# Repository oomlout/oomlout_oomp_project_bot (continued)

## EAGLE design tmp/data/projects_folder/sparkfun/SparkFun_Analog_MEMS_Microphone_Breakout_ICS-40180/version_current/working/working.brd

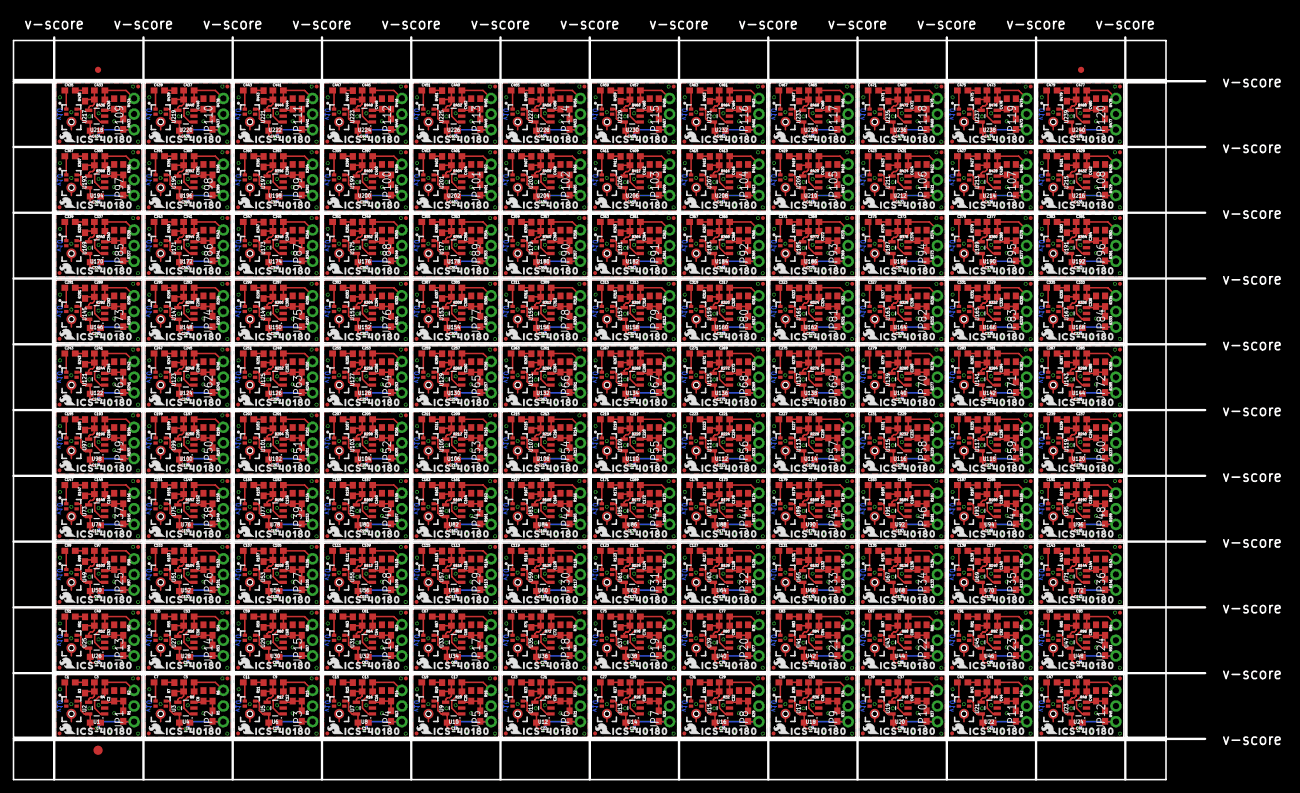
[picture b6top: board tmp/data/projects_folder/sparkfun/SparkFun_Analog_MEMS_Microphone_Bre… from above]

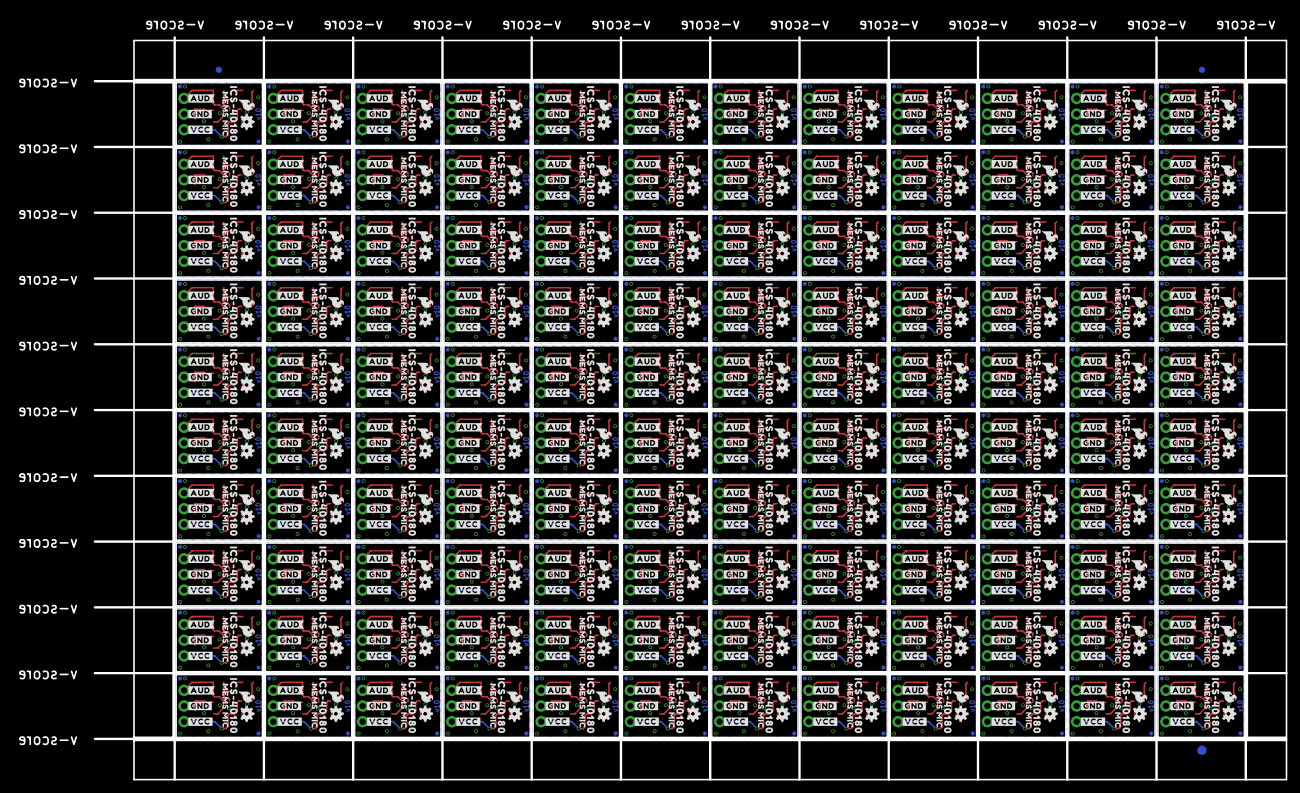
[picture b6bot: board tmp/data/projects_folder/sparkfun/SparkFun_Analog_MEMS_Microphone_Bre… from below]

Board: 2 copper layers, 193.3 x 120.4 mm, 2886 parts (1083 on the bottom side), 840 nets.

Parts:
C1, C7, C11, C15, C19, C23, C27, C31, C35, C39, C43, C47, C51, C55, C59, C63, C67, C71, C75, C79, C83, C87, C91, C95, C99, C103, C107, C111, C115, C119, C123, C127, C131, C135, C139, C143, C147, C151, C155, C159, C163, C167, C171, C175, C179, C183, C187, C191, C195, C199, C203, C207, C211, C215, C219, C223, C227, C231, C235, C239, C243, C247, C251, C255, C259, C263, C267, C271, C275, C279, C283, C287, C291, C295, C299, C303, C307, C311, C315, C319, C323, C327, C331, C335, C339, C343, C347, C351, C355, C359, C363, C367, C371, C375, C379, C383, C387, C391, C395, C399, C403, C407, C411, C415, C419, C423, C427, C431, C435, C439, C443, C447, C451, C455, C459, C463, C467, C471, C475, C479: 4.7uF; 0603
C2, C8, C12, C16, C20, C24, C28, C32, C36, C40, C44, C48, C52, C56, C60, C64, C68, C72, C76, C80, C84, C88, C92, C96, C100, C104, C108, C112, C116, C120, C124, C128, C132, C136, C140, C144, C148, C152, C156, C160, C164, C168, C172, C176, C180, C184, C188, C192, C196, C200, C204, C208, C212, C216, C220, C224, C228, C232, C236, C240, C244, C248, C252, C256, C260, C264, C268, C272, C276, C280, C284, C288, C292, C296, C300, C304, C308, C312, C316, C320, C324, C328, C332, C336, C340, C344, C348, C352, C356, C360, C364, C368, C372, C376, C380, C384, C388, C392, C396, C400, C404, C408, C412, C416, C420, C424, C428, C432, C436, C440, C444, C448, C452, C456, C460, C464, C468, C472, C476, C480: 1.0uF; 0603
C3, C5, C9, C13, C17, C21, C25, C29, C33, C37, C41, C45, C49, C53, C57, C61, C65, C69, C73, C77, C81, C85, C89, C93, C97, C101, C105, C109, C113, C117, C121, C125, C129, C133, C137, C141, C145, C149, C153, C157, C161, C165, C169, C173, C177, C181, C185, C189, C193, C197, C201, C205, C209, C213, C217, C221, C225, C229, C233, C237, C241, C245, C249, C253, C257, C261, C265, C269, C273, C277, C281, C285, C289, C293, C297, C301, C305, C309, C313, C317, C321, C325, C329, C333, C337, C341, C345, C349, C353, C357, C361, C365, C369, C373, C377, C381, C385, C389, C393, C397, C401, C405, C409, C413, C417, C421, C425, C429, C433, C437, C441, C445, C449, C453, C457, C461, C465, C469, C473, C477: 27pF; 0603
C4, C6, C10, C14, C18, C22, C26, C30, C34, C38, C42, C46, C50, C54, C58, C62, C66, C70, C74, C78, C82, C86, C90, C94, C98, C102, C106, C110, C114, C118, C122, C126, C130, C134, C138, C142, C146, C150, C154, C158, C162, C166, C170, C174, C178, C182, C186, C190, C194, C198, C202, C206, C210, C214, C218, C222, C226, C230, C234, C238, C242, C246, C250, C254, C258, C262, C266, C270, C274, C278, C282, C286, C290, C294, C298, C302, C306, C310, C314, C318, C322, C326, C330, C334, C338, C342, C346, C350, C354, C358, C362, C366, C370, C374, C378, C382, C386, C390, C394, C398, C402, C406, C410, C414, C418, C422, C426, C430, C434, C438, C442, C446, C450, C454, C458, C462, C466, C470, C474, C478: 0.1uF; 0603
E$1, E$2, E$3, E$4: FIDUCIAL-1X2
E$5, E$6: FIDUCIAL-1.5X3
FD1, FD2, FD3, FD4, FD5, FD6, FD7, FD8, FD9, FD10, FD11, FD12, FD13, FD14, FD15, FD16, FD17, FD18, FD19, FD20, FD21, FD22, FD23, FD24, FD25, FD26, FD27, FD28, FD29, FD30, FD31, FD32, FD33, FD34, FD35, FD36, FD37, FD38, FD39, FD40, FD41, FD42, FD43, FD44, FD45, FD46, FD47, FD48, FD49, FD50, FD51, FD52, FD53, FD54, FD55, FD56, FD57, FD58, FD59, FD60, FD61, FD62, FD63, FD64, FD65, FD66, FD67, FD68, FD69, FD70, FD71, FD72, FD73, FD74, FD75, FD76, FD77, FD78, FD79, FD80, FD81, FD82, FD83, FD84, FD85, FD86, FD87, FD88, FD89, FD90, FD91, FD92, FD93, FD94, FD95, FD96, FD97, FD98, FD99, FD100, FD101, FD102, FD103, FD104, FD105, FD106, FD107, FD108, FD109, FD110, FD111, FD112, FD113, FD114, FD115, FD116, FD117, FD118, FD119, FD120, FD121, FD122, FD123, FD124, FD125, FD126, FD127, FD128, FD129, FD130, FD131, FD132, FD133, FD134, FD135, FD136, FD137, FD138, FD139, FD140, FD141, FD142, FD143, FD144, FD145, FD146, FD147, FD148, FD149, FD150, FD151, FD152, FD153, FD154, FD155, FD156, FD157, FD158, FD159, FD160, FD161, FD162, FD163, FD164, FD165, FD166, FD167, FD168, FD169, FD170, FD171, FD172, FD173, FD174, FD175, FD176, FD177, FD178, FD179, FD180, FD181, FD182, FD183, FD184, FD185, FD186, FD187, FD188, FD189, FD190, FD191, FD192, FD193, FD194, FD195, FD196, FD197, FD198, FD199, FD200, FD201, FD202, FD203, FD204, FD205, FD206, FD207, FD208, FD209, FD210, FD211, FD212, FD213, FD214, FD215, FD216, FD217, FD218, FD219, FD220, FD221, FD222, FD223, FD224, FD225, FD226, FD227, FD228, FD229, FD230, FD231, FD232, FD233, FD234, FD235, FD236, FD237, FD238, FD239, FD240, FD241, FD242, FD243, FD244, FD245, FD246, FD247, FD248, FD249, FD250, FD251, FD252, FD253, FD254, FD255, FD256, FD257, FD258, FD259, FD260, FD261, FD262, FD263, FD264, FD265, FD266, FD267, FD268, FD269, FD270, FD271, FD272, FD273, FD274, FD275, FD276, FD277, FD278, FD279, FD280, FD281, FD282, FD283, FD284, FD285, FD286, FD287, FD288, FD289, FD290, FD291, FD292, FD293, FD294, FD295, FD296, FD297, FD298, FD299, FD300, FD301, FD302, FD303, FD304, FD305, FD306, FD307, FD308, FD309, FD310, FD311, FD312, FD313, FD314, FD315, FD316, FD317, FD318, FD319, FD320, FD321, FD322, FD323, FD324, FD325, FD326, FD327, FD328, FD329, FD330, FD331, FD332, FD333, FD334, FD335, FD336, FD337, FD338, FD339, FD340, FD341, FD342, FD343, FD344, FD345, FD346, FD347, FD348, FD349, FD350, FD351, FD352, FD353, FD354, FD355, FD356, FD357, FD358, FD359, FD360, FD361, FD362, FD363, FD364, FD365, FD366, FD367, FD368, FD369, FD370, FD371, FD372, FD373, FD374, FD375, FD376, FD377, FD378, FD379, FD380, FD381, FD382, FD383, FD384, FD385, FD386, FD387, FD388, FD389, FD390, FD391, FD392, FD393, FD394, FD395, FD396, FD397, FD398, FD399, FD400, FD401, FD402, FD403, FD404, FD405, FD406, FD407, FD408, FD409, FD410, FD411, FD412, FD413, FD414, FD415, FD416, FD417, FD418, FD419, FD420, FD421, FD422, FD423, FD424, FD425, FD426, FD427, FD428, FD429, FD430, FD431, FD432, FD433, FD434, FD435, FD436, FD437, FD438, FD439, FD440, FD441, FD442, FD443, FD444, FD445, FD446, FD447, FD448, FD449, FD450, FD451, FD452, FD453, FD454, FD455, FD456, FD457, FD458, FD459, FD460, FD461, FD462, FD463, FD464, FD465, FD466, FD467, FD468, FD469, FD470, FD471, FD472, FD473, FD474, FD475, FD476, FD477, FD478, FD479, FD480: FIDUCIALUFIDUCIAL; FIDUCIAL-MICRO
JP1, JP2, JP3, JP4, JP5, JP6, JP7, JP8, JP9, JP10, JP11, JP12, JP13, JP14, JP15, JP16, JP17, JP18, JP19, JP20, JP21, JP22, JP23, JP24, JP25, JP26, JP27, JP28, JP29, JP30, JP31, JP32, JP33, JP34, JP35, JP36, JP37, JP38, JP39, JP40, JP41, JP42, JP43, JP44, JP45, JP46, JP47, JP48, JP49, JP50, JP51, JP52, JP53, JP54, JP55, JP56, JP57, JP58, JP59, JP60, JP61, JP62, JP63, JP64, JP65, JP66, JP67, JP68, JP69, JP70, JP71, JP72, JP73, JP74, JP75, JP76, JP77, JP78, JP79, JP80, JP81, JP82, JP83, JP84, JP85, JP86, JP87, JP88, JP89, JP90, JP91, JP92, JP93, JP94, JP95, JP96, JP97, JP98, JP99, JP100, JP101, JP102, JP103, JP104, JP105, JP106, JP107, JP108, JP109, JP110, JP111, JP112, JP113, JP114, JP115, JP116, JP117, JP118, JP119, JP120: 1X03_NO_SILK
LOGO1, LOGO3, LOGO4, LOGO6, LOGO7, LOGO9, LOGO10, LOGO12, LOGO13, LOGO15, LOGO16, LOGO18, LOGO19, LOGO21, LOGO22, LOGO24, LOGO25, LOGO27, LOGO28, LOGO30, LOGO31, LOGO33, LOGO34, LOGO36, LOGO37, LOGO39, LOGO40, LOGO42, LOGO43, LOGO45, LOGO46, LOGO48, LOGO49, LOGO51, LOGO52, LOGO54, LOGO55, LOGO57, LOGO58, LOGO60, LOGO61, LOGO63, LOGO64, LOGO66, LOGO67, LOGO69, LOGO70, LOGO72, LOGO73, LOGO75, LOGO76, LOGO78, LOGO79, LOGO81, LOGO82, LOGO84, LOGO85, LOGO87, LOGO88, LOGO90, LOGO91, LOGO93, LOGO94, LOGO96, LOGO97, LOGO99, LOGO100, LOGO102, LOGO103, LOGO105, LOGO106, LOGO108, LOGO109, LOGO111, LOGO112, LOGO114, LOGO115, LOGO117, LOGO118, LOGO120, LOGO121, LOGO123, LOGO124, LOGO126, LOGO127, LOGO129, LOGO130, LOGO132, LOGO133, LOGO135, LOGO136, LOGO138, LOGO139, LOGO141, LOGO142, LOGO144, LOGO145, LOGO147, LOGO148, LOGO150, LOGO151, LOGO153, LOGO154, LOGO156, LOGO157, LOGO159, LOGO160, LOGO162, LOGO163, LOGO165, LOGO166, LOGO168, LOGO169, LOGO171, LOGO172, LOGO174, LOGO175, LOGO177, LOGO178, LOGO180, LOGO181, LOGO183, LOGO184, LOGO186, LOGO187, LOGO189, LOGO190, LOGO192, LOGO193, LOGO195, LOGO196, LOGO198, LOGO199, LOGO201, LOGO202, LOGO204, LOGO205, LOGO207, LOGO208, LOGO210, LOGO211, LOGO213, LOGO214, LOGO216, LOGO217, LOGO219, LOGO220, LOGO222, LOGO223, LOGO225, LOGO226, LOGO228, LOGO229, LOGO231, LOGO232, LOGO234, LOGO235, LOGO237, LOGO238, LOGO240, LOGO241, LOGO243, LOGO244, LOGO246, LOGO247, LOGO249, LOGO250, LOGO252, LOGO253, LOGO255, LOGO256, LOGO258, LOGO259, LOGO261, LOGO262, LOGO264, LOGO265, LOGO267, LOGO268, LOGO270, LOGO271, LOGO273, LOGO274, LOGO276, LOGO277, LOGO279, LOGO280, LOGO282, LOGO283, LOGO285, LOGO286, LOGO288, LOGO289, LOGO291, LOGO292, LOGO294, LOGO295, LOGO297, LOGO298, LOGO300, LOGO301, LOGO303, LOGO304, LOGO306, LOGO307, LOGO309, LOGO310, LOGO312, LOGO313, LOGO315, LOGO316, LOGO318, LOGO319, LOGO321, LOGO322, LOGO324, LOGO325, LOGO327, LOGO328, LOGO330, LOGO331, LOGO333, LOGO334, LOGO336, LOGO337, LOGO339, LOGO340, LOGO342, LOGO343, LOGO345, LOGO346, LOGO348, LOGO349, LOGO351, LOGO352, LOGO354, LOGO355, LOGO357, LOGO358, LOGO360: SFE_LOGO_FLAME.1_INCH; SFE_LOGO_FLAME_.1
LOGO2, LOGO5, LOGO8, LOGO11, LOGO14, LOGO17, LOGO20, LOGO23, LOGO26, LOGO29, LOGO32, LOGO35, LOGO38, LOGO41, LOGO44, LOGO47, LOGO50, LOGO53, LOGO56, LOGO59, LOGO62, LOGO65, LOGO68, LOGO71, LOGO74, LOGO77, LOGO80, LOGO83, LOGO86, LOGO89, LOGO92, LOGO95, LOGO98, LOGO101, LOGO104, LOGO107, LOGO110, LOGO113, LOGO116, LOGO119, LOGO122, LOGO125, LOGO128, LOGO131, LOGO134, LOGO137, LOGO140, LOGO143, LOGO146, LOGO149, LOGO152, LOGO155, LOGO158, LOGO161, LOGO164, LOGO167, LOGO170, LOGO173, LOGO176, LOGO179, LOGO182, LOGO185, LOGO188, LOGO191, LOGO194, LOGO197, LOGO200, LOGO203, LOGO206, LOGO209, LOGO212, LOGO215, LOGO218, LOGO221, LOGO224, LOGO227, LOGO230, LOGO233, LOGO236, LOGO239, LOGO242, LOGO245, LOGO248, LOGO251, LOGO254, LOGO257, LOGO260, LOGO263, LOGO266, LOGO269, LOGO272, LOGO275, LOGO278, LOGO281, LOGO284, LOGO287, LOGO290, LOGO293, LOGO296, LOGO299, LOGO302, LOGO305, LOGO308, LOGO311, LOGO314, LOGO317, LOGO320, LOGO323, LOGO326, LOGO329, LOGO332, LOGO335, LOGO338, LOGO341, LOGO344, LOGO347, LOGO350, LOGO353, LOGO356, LOGO359: OSHW-LOGOMINI; OSHW-LOGO-MINI
R1, R2, R5, R6, R9, R10, R13, R14, R17, R18, R21, R22, R25, R26, R29, R30, R33, R34, R37, R38, R41, R42, R45, R46, R49, R50, R53, R54, R57, R58, R61, R62, R65, R66, R69, R70, R73, R74, R77, R78, R81, R82, R85, R86, R89, R90, R93, R94, R97, R98, R101, R102, R105, R106, R109, R110, R113, R114, R117, R118, R121, R122, R125, R126, R129, R130, R133, R134, R137, R138, R141, R142, R145, R146, R149, R150, R153, R154, R157, R158, R161, R162, R165, R166, R169, R170, R173, R174, R177, R178, R181, R182, R185, R186, R189, R190, R193, R194, R197, R198, R201, R202, R205, R206, R209, R210, R213, R214, R217, R218, R221, R222, R225, R226, R229, R230, R233, R234, R237, R238, R241, R242, R245, R246, R249, R250, R253, R254, R257, R258, R261, R262, R265, R266, R269, R270, R273, R274, R277, R278, R281, R282, R285, R286, R289, R290, R293, R294, R297, R298, R301, R302, R305, R306, R309, R310, R313, R314, R317, R318, R321, R322, R325, R326, R329, R330, R333, R334, R337, R338, R341, R342, R345, R346, R349, R350, R353, R354, R357, R358, R361, R362, R365, R366, R369, R370, R373, R374, R377, R378, R381, R382, R385, R386, R389, R390, R393, R394, R397, R398, R401, R402, R405, R406, R409, R410, R413, R414, R417, R418, R421, R422, R425, R426, R429, R430, R433, R434, R437, R438, R441, R442, R445, R446, R449, R450, R453, R454, R457, R458, R461, R462, R465, R466, R469, R470, R473, R474, R477, R478: 10k; 0603
R3, R7, R11, R15, R19, R23, R27, R31, R35, R39, R43, R47, R51, R55, R59, R63, R67, R71, R75, R79, R83, R87, R91, R95, R99, R103, R107, R111, R115, R119, R123, R127, R131, R135, R139, R143, R147, R151, R155, R159, R163, R167, R171, R175, R179, R183, R187, R191, R195, R199, R203, R207, R211, R215, R219, R223, R227, R231, R235, R239, R243, R247, R251, R255, R259, R263, R267, R271, R275, R279, R283, R287, R291, R295, R299, R303, R307, R311, R315, R319, R323, R327, R331, R335, R339, R343, R347, R351, R355, R359, R363, R367, R371, R375, R379, R383, R387, R391, R395, R399, R403, R407, R411, R415, R419, R423, R427, R431, R435, R439, R443, R447, R451, R455, R459, R463, R467, R471, R475, R479: 4.7k; 0603
R4, R8, R12, R16, R20, R24, R28, R32, R36, R40, R44, R48, R52, R56, R60, R64, R68, R72, R76, R80, R84, R88, R92, R96, R100, R104, R108, R112, R116, R120, R124, R128, R132, R136, R140, R144, R148, R152, R156, R160, R164, R168, R172, R176, R180, R184, R188, R192, R196, R200, R204, R208, R212, R216, R220, R224, R228, R232, R236, R240, R244, R248, R252, R256, R260, R264, R268, R272, R276, R280, R284, R288, R292, R296, R300, R304, R308, R312, R316, R320, R324, R328, R332, R336, R340, R344, R348, R352, R356, R360, R364, R368, R372, R376, R380, R384, R388, R392, R396, R400, R404, R408, R412, R416, R420, R424, R428, R432, R436, R440, R444, R448, R452, R456, R460, R464, R468, R472, R476, R480: 300k; 0603
U1, U4, U6, U8, U10, U12, U14, U16, U18, U20, U22, U24, U26, U28, U30, U32, U34, U36, U38, U40, U42, U44, U46, U48, U50, U52, U54, U56, U58, U60, U62, U64, U66, U68, U70, U72, U74, U76, U78, U80, U82, U84, U86, U88, U90, U92, U94, U96, U98, U100, U102, U104, U106, U108, U110, U112, U114, U116, U118, U120, U122, U124, U126, U128, U130, U132, U134, U136, U138, U140, U142, U144, U146, U148, U150, U152, U154, U156, U158, U160, U162, U164, U166, U168, U170, U172, U174, U176, U178, U180, U182, U184, U186, U188, U190, U192, U194, U196, U198, U200, U202, U204, U206, U208, U210, U212, U214, U216, U218, U220, U222, U224, U226, U228, U230, U232, U234, U236, U238, U240: OPA344; SOT23-5
U2, U3, U5, U7, U9, U11, U13, U15, U17, U19, U21, U23, U25, U27, U29, U31, U33, U35, U37, U39, U41, U43, U45, U47, U49, U51, U53, U55, U57, U59, U61, U63, U65, U67, U69, U71, U73, U75, U77, U79, U81, U83, U85, U87, U89, U91, U93, U95, U97, U99, U101, U103, U105, U107, U109, U111, U113, U115, U117, U119, U121, U123, U125, U127, U129, U131, U133, U135, U137, U139, U141, U143, U145, U147, U149, U151, U153, U155, U157, U159, U161, U163, U165, U167, U169, U171, U173, U175, U177, U179, U181, U183, U185, U187, U189, U191, U193, U195, U197, U199, U201, U203, U205, U207, U209, U211, U213, U215, U217, U219, U221, U223, U225, U227, U229, U231, U233, U235, U237, U239: ICS40180
U$1, U$6, U$7, U$12, U$13, U$18, U$19, U$24, U$25, U$30, U$31, U$36, U$37, U$42, U$43, U$48, U$49, U$54, U$55, U$60, U$61, U$66, U$67, U$72, U$73, U$78, U$79, U$84, U$85, U$90, U$91, U$96, U$97, U$102, U$103, U$108, U$109, U$114, U$115, U$120, U$121, U$126, U$127, U$132, U$133, U$138, U$139, U$144, U$145, U$150, U$151, U$156, U$157, U$162, U$163, U$168, U$169, U$174, U$175, U$180, U$181, U$186, U$187, U$192, U$193, U$198, U$199, U$204, U$205, U$210, U$211, U$216, U$217, U$222, U$223, U$228, U$229, U$234, U$235, U$240, U$241, U$246, U$247, U$252, U$253, U$258, U$259, U$264, U$265, U$270, U$271, U$276, U$277, U$282, U$283, U$288, U$289, U$294, U$295, U$300, U$301, U$306, U$307, U$312, U$313, U$318, U$319, U$324, U$325, U$330, U$331, U$336, U$337, U$342, U$343, U$348, U$349, U$354, U$355, U$360, U$361, U$366, U$367, U$372, U$373, U$378, U$379, U$384, U$385, U$390, U$391, U$396, U$397, U$402, U$403, U$408, U$409, U$414, U$415, U$420, U$421, U$426, U$427, U$432, U$433, U$438, U$439, U$444, U$445, U$450, U$451, U$456, U$457, U$462, U$463, U$468, U$469, U$474, U$475, U$480, U$481, U$486, U$487, U$492, U$493, U$498, U$499, U$504, U$505, U$510, U$511, U$516, U$517, U$522, U$523, U$528, U$529, U$534, U$535, U$540, U$541, U$546, U$547, U$552, U$553, U$558, U$559, U$564, U$565, U$570, U$571, U$576, U$577, U$582, U$583, U$588, U$589, U$594, U$595, U$600, U$601, U$606, U$607, U$612, U$613, U$618, U$619, U$624, U$625, U$630, U$631, U$636, U$637, U$642, U$643, U$648, U$649, U$654, U$655, U$660, U$661, U$666, U$667, U$672, U$673, U$678, U$679, U$684, U$685, U$690, U$691, U$696, U$697, U$702, U$703, U$708, U$709, U$714, U$715, U$720: ICS#401800
U$2, U$8, U$14, U$20, U$26, U$32, U$38, U$44, U$50, U$56, U$62, U$68, U$74, U$80, U$86, U$92, U$98, U$104, U$110, U$116, U$122, U$128, U$134, U$140, U$146, U$152, U$158, U$164, U$170, U$176, U$182, U$188, U$194, U$200, U$206, U$212, U$218, U$224, U$230, U$236, U$242, U$248, U$254, U$260, U$266, U$272, U$278, U$284, U$290, U$296, U$302, U$308, U$314, U$320, U$326, U$332, U$338, U$344, U$350, U$356, U$362, U$368, U$374, U$380, U$386, U$392, U$398, U$404, U$410, U$416, U$422, U$428, U$434, U$440, U$446, U$452, U$458, U$464, U$470, U$476, U$482, U$488, U$494, U$500, U$506, U$512, U$518, U$524, U$530, U$536, U$542, U$548, U$554, U$560, U$566, U$572, U$578, U$584, U$590, U$596, U$602, U$608, U$614, U$620, U$626, U$632, U$638, U$644, U$650, U$656, U$662, U$668, U$674, U$680, U$686, U$692, U$698, U$704, U$710, U$716: MEMS_MIC0
U$3, U$9, U$15, U$21, U$27, U$33, U$39, U$45, U$51, U$57, U$63, U$69, U$75, U$81, U$87, U$93, U$99, U$105, U$111, U$117, U$123, U$129, U$135, U$141, U$147, U$153, U$159, U$165, U$171, U$177, U$183, U$189, U$195, U$201, U$207, U$213, U$219, U$225, U$231, U$237, U$243, U$249, U$255, U$261, U$267, U$273, U$279, U$285, U$291, U$297, U$303, U$309, U$315, U$321, U$327, U$333, U$339, U$345, U$351, U$357, U$363, U$369, U$375, U$381, U$387, U$393, U$399, U$405, U$411, U$417, U$423, U$429, U$435, U$441, U$447, U$453, U$459, U$465, U$471, U$477, U$483, U$489, U$495, U$501, U$507, U$513, U$519, U$525, U$531, U$537, U$543, U$549, U$555, U$561, U$567, U$573, U$579, U$585, U$591, U$597, U$603, U$609, U$615, U$621, U$627, U$633, U$639, U$645, U$651, U$657, U$663, U$669, U$675, U$681, U$687, U$693, U$699, U$705, U$711, U$717: #GND#0
U$4, U$10, U$16, U$22, U$28, U$34, U$40, U$46, U$52, U$58, U$64, U$70, U$76, U$82, U$88, U$94, U$100, U$106, U$112, U$118, U$124, U$130, U$136, U$142, U$148, U$154, U$160, U$166, U$172, U$178, U$184, U$190, U$196, U$202, U$208, U$214, U$220, U$226, U$232, U$238, U$244, U$250, U$256, U$262, U$268, U$274, U$280, U$286, U$292, U$298, U$304, U$310, U$316, U$322, U$328, U$334, U$340, U$346, U$352, U$358, U$364, U$370, U$376, U$382, U$388, U$394, U$400, U$406, U$412, U$418, U$424, U$430, U$436, U$442, U$448, U$454, U$460, U$466, U$472, U$478, U$484, U$490, U$496, U$502, U$508, U$514, U$520, U$526, U$532, U$538, U$544, U$550, U$556, U$562, U$568, U$574, U$580, U$586, U$592, U$598, U$604, U$610, U$616, U$622, U$628, U$634, U$640, U$646, U$652, U$658, U$664, U$670, U$676, U$682, U$688, U$694, U$700, U$706, U$712, U$718: #VCC#0
U$5, U$11, U$17, U$23, U$29, U$35, U$41, U$47, U$53, U$59, U$65, U$71, U$77, U$83, U$89, U$95, U$101, U$107, U$113, U$119, U$125, U$131, U$137, U$143, U$149, U$155, U$161, U$167, U$173, U$179, U$185, U$191, U$197, U$203, U$209, U$215, U$221, U$227, U$233, U$239, U$245, U$251, U$257, U$263, U$269, U$275, U$281, U$287, U$293, U$299, U$305, U$311, U$317, U$323, U$329, U$335, U$341, U$347, U$353, U$359, U$365, U$371, U$377, U$383, U$389, U$395, U$401, U$407, U$413, U$419, U$425, U$431, U$437, U$443, U$449, U$455, U$461, U$467, U$473, U$479, U$485, U$491, U$497, U$503, U$509, U$515, U$521, U$527, U$533, U$539, U$545, U$551, U$557, U$563, U$569, U$575, U$581, U$587, U$593, U$599, U$605, U$611, U$617, U$623, U$629, U$635, U$641, U$647, U$653, U$659, U$665, U$671, U$677, U$683, U$689, U$695, U$701, U$707, U$713, U$719: #AUD#0

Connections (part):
AUD: C3.2, JP1.3, R4.1, U1.1
AUD1: C5.2, JP2.3, R8.1, U4.1
AUD2: C9.2, JP3.3, R12.1, U6.1
AUD3: C13.2, JP4.3, R16.1, U8.1
AUD4: C17.2, JP5.3, R20.1, U10.1
AUD5: C21.2, JP6.3, R24.1, U12.1
AUD6: C25.2, JP7.3, R28.1, U14.1
AUD7: C29.2, JP8.3, R32.1, U16.1
AUD8: C33.2, JP9.3, R36.1, U18.1
AUD9: C37.2, JP10.3, R40.1, U20.1
AUD10: C41.2, JP11.3, R44.1, U22.1
AUD11: C45.2, JP12.3, R48.1, U24.1
AUD12: C49.2, JP13.3, R52.1, U26.1
AUD13: C53.2, JP14.3, R56.1, U28.1
AUD14: C57.2, JP15.3, R60.1, U30.1
AUD15: C61.2, JP16.3, R64.1, U32.1
AUD16: C65.2, JP17.3, R68.1, U34.1
AUD17: C69.2, JP18.3, R72.1, U36.1
AUD18: C73.2, JP19.3, R76.1, U38.1
AUD19: C77.2, JP20.3, R80.1, U40.1
AUD20: C81.2, JP21.3, R84.1, U42.1
AUD21: C85.2, JP22.3, R88.1, U44.1
AUD22: C89.2, JP23.3, R92.1, U46.1
AUD23: C93.2, JP24.3, R96.1, U48.1
AUD24: C97.2, JP25.3, R100.1, U50.1
AUD25: C101.2, JP26.3, R104.1, U52.1
AUD26: C105.2, JP27.3, R108.1, U54.1
AUD27: C109.2, JP28.3, R112.1, U56.1
AUD28: C113.2, JP29.3, R116.1, U58.1
AUD29: C117.2, JP30.3, R120.1, U60.1
AUD30: C121.2, JP31.3, R124.1, U62.1
AUD31: C125.2, JP32.3, R128.1, U64.1
AUD32: C129.2, JP33.3, R132.1, U66.1
AUD33: C133.2, JP34.3, R136.1, U68.1
AUD34: C137.2, JP35.3, R140.1, U70.1
AUD35: C141.2, JP36.3, R144.1, U72.1
AUD36: C145.2, JP37.3, R148.1, U74.1
AUD37: C149.2, JP38.3, R152.1, U76.1
AUD38: C153.2, JP39.3, R156.1, U78.1
AUD39: C157.2, JP40.3, R160.1, U80.1
AUD40: C161.2, JP41.3, R164.1, U82.1
AUD41: C165.2, JP42.3, R168.1, U84.1
AUD42: C169.2, JP43.3, R172.1, U86.1
AUD43: C173.2, JP44.3, R176.1, U88.1
AUD44: C177.2, JP45.3, R180.1, U90.1
AUD45: C181.2, JP46.3, R184.1, U92.1
AUD46: C185.2, JP47.3, R188.1, U94.1
AUD47: C189.2, JP48.3, R192.1, U96.1
AUD48: C193.2, JP49.3, R196.1, U98.1
AUD49: C197.2, JP50.3, R200.1, U100.1
AUD50: C201.2, JP51.3, R204.1, U102.1
AUD51: C205.2, JP52.3, R208.1, U104.1
AUD52: C209.2, JP53.3, R212.1, U106.1
AUD53: C213.2, JP54.3, R216.1, U108.1
AUD54: C217.2, JP55.3, R220.1, U110.1
AUD55: C221.2, JP56.3, R224.1, U112.1
AUD56: C225.2, JP57.3, R228.1, U114.1
AUD57: C229.2, JP58.3, R232.1, U116.1
AUD58: C233.2, JP59.3, R236.1, U118.1
AUD59: C237.2, JP60.3, R240.1, U120.1
AUD60: C241.2, JP61.3, R244.1, U122.1
AUD61: C245.2, JP62.3, R248.1, U124.1
AUD62: C249.2, JP63.3, R252.1, U126.1
AUD63: C253.2, JP64.3, R256.1, U128.1
AUD64: C257.2, JP65.3, R260.1, U130.1
AUD65: C261.2, JP66.3, R264.1, U132.1
AUD66: C265.2, JP67.3, R268.1, U134.1
AUD67: C269.2, JP68.3, R272.1, U136.1
AUD68: C273.2, JP69.3, R276.1, U138.1
AUD69: C277.2, JP70.3, R280.1, U140.1
AUD70: C281.2, JP71.3, R284.1, U142.1
AUD71: C285.2, JP72.3, R288.1, U144.1
AUD72: C289.2, JP73.3, R292.1, U146.1
AUD73: C293.2, JP74.3, R296.1, U148.1
AUD74: C297.2, JP75.3, R300.1, U150.1
AUD75: C301.2, JP76.3, R304.1, U152.1
AUD76: C305.2, JP77.3, R308.1, U154.1
AUD77: C309.2, JP78.3, R312.1, U156.1
AUD78: C313.2, JP79.3, R316.1, U158.1
AUD79: C317.2, JP80.3, R320.1, U160.1
AUD80: C321.2, JP81.3, R324.1, U162.1
AUD81: C325.2, JP82.3, R328.1, U164.1
AUD82: C329.2, JP83.3, R332.1, U166.1
AUD83: C333.2, JP84.3, R336.1, U168.1
AUD84: C337.2, JP85.3, R340.1, U170.1
AUD85: C341.2, JP86.3, R344.1, U172.1
AUD86: C345.2, JP87.3, R348.1, U174.1
AUD87: C349.2, JP88.3, R352.1, U176.1
AUD88: C353.2, JP89.3, R356.1, U178.1
AUD89: C357.2, JP90.3, R360.1, U180.1
AUD90: C361.2, JP91.3, R364.1, U182.1
AUD91: C365.2, JP92.3, R368.1, U184.1
AUD92: C369.2, JP93.3, R372.1, U186.1
AUD93: C373.2, JP94.3, R376.1, U188.1
AUD94: C377.2, JP95.3, R380.1, U190.1
AUD95: C381.2, JP96.3, R384.1, U192.1
AUD96: C385.2, JP97.3, R388.1, U194.1
AUD97: C389.2, JP98.3, R392.1, U196.1
AUD98: C393.2, JP99.3, R396.1, U198.1
AUD99: C397.2, JP100.3, R400.1, U200.1
AUD100: C401.2, JP101.3, R404.1, U202.1
AUD101: C405.2, JP102.3, R408.1, U204.1
AUD102: C409.2, JP103.3, R412.1, U206.1
AUD103: C413.2, JP104.3, R416.1, U208.1
AUD104: C417.2, JP105.3, R420.1, U210.1
AUD105: C421.2, JP106.3, R424.1, U212.1
AUD106: C425.2, JP107.3, R428.1, U214.1
AUD107: C429.2, JP108.3, R432.1, U216.1
AUD108: C433.2, JP109.3, R436.1, U218.1
AUD109: C437.2, JP110.3, R440.1, U220.1
AUD110: C441.2, JP111.3, R444.1, U222.1
AUD111: C445.2, JP112.3, R448.1, U224.1
AUD112: C449.2, JP113.3, R452.1, U226.1
AUD113: C453.2, JP114.3, R456.1, U228.1
AUD114: C457.2, JP115.3, R460.1, U230.1
AUD115: C461.2, JP116.3, R464.1, U232.1
AUD116: C465.2, JP117.3, R468.1, U234.1
AUD117: C469.2, JP118.3, R472.1, U236.1
AUD118: C473.2, JP119.3, R476.1, U238.1
AUD119: C477.2, JP120.3, R480.1, U240.1
GND: C2.2, C4.1, JP1.2, R2.1, U1.2, U2.2, U2.3, U2.4
GND1: C6.1, C8.2, JP2.2, R6.1, U3.2, U3.3, U3.4, U4.2
GND2: C10.1, C12.2, JP3.2, R10.1, U5.2, U5.3, U5.4, U6.2
GND3: C14.1, C16.2, JP4.2, R14.1, U7.2, U7.3, U7.4, U8.2
GND4: C18.1, C20.2, JP5.2, R18.1, U9.2, U9.3, U9.4, U10.2
GND5: C22.1, C24.2, JP6.2, R22.1, U11.2, U11.3, U11.4, U12.2
GND6: C26.1, C28.2, JP7.2, R26.1, U13.2, U13.3, U13.4, U14.2
GND7: C30.1, C32.2, JP8.2, R30.1, U15.2, U15.3, U15.4, U16.2
GND8: C34.1, C36.2, JP9.2, R34.1, U17.2, U17.3, U17.4, U18.2
GND9: C38.1, C40.2, JP10.2, R38.1, U19.2, U19.3, U19.4, U20.2
GND10: C42.1, C44.2, JP11.2, R42.1, U21.2, U21.3, U21.4, U22.2
GND11: C46.1, C48.2, JP12.2, R46.1, U23.2, U23.3, U23.4, U24.2
GND12: C50.1, C52.2, JP13.2, R50.1, U25.2, U25.3, U25.4, U26.2
GND13: C54.1, C56.2, JP14.2, R54.1, U27.2, U27.3, U27.4, U28.2
GND14: C58.1, C60.2, JP15.2, R58.1, U29.2, U29.3, U29.4, U30.2
GND15: C62.1, C64.2, JP16.2, R62.1, U31.2, U31.3, U31.4, U32.2
GND16: C66.1, C68.2, JP17.2, R66.1, U33.2, U33.3, U33.4, U34.2
GND17: C70.1, C72.2, JP18.2, R70.1, U35.2, U35.3, U35.4, U36.2
GND18: C74.1, C76.2, JP19.2, R74.1, U37.2, U37.3, U37.4, U38.2
GND19: C78.1, C80.2, JP20.2, R78.1, U39.2, U39.3, U39.4, U40.2
GND20: C82.1, C84.2, JP21.2, R82.1, U41.2, U41.3, U41.4, U42.2
GND21: C86.1, C88.2, JP22.2, R86.1, U43.2, U43.3, U43.4, U44.2
GND22: C90.1, C92.2, JP23.2, R90.1, U45.2, U45.3, U45.4, U46.2
GND23: C94.1, C96.2, JP24.2, R94.1, U47.2, U47.3, U47.4, U48.2
GND24: C98.1, C100.2, JP25.2, R98.1, U49.2, U49.3, U49.4, U50.2
GND25: C102.1, C104.2, JP26.2, R102.1, U51.2, U51.3, U51.4, U52.2
GND26: C106.1, C108.2, JP27.2, R106.1, U53.2, U53.3, U53.4, U54.2
GND27: C110.1, C112.2, JP28.2, R110.1, U55.2, U55.3, U55.4, U56.2
GND28: C114.1, C116.2, JP29.2, R114.1, U57.2, U57.3, U57.4, U58.2
GND29: C118.1, C120.2, JP30.2, R118.1, U59.2, U59.3, U59.4, U60.2
GND30: C122.1, C124.2, JP31.2, R122.1, U61.2, U61.3, U61.4, U62.2
GND31: C126.1, C128.2, JP32.2, R126.1, U63.2, U63.3, U63.4, U64.2
GND32: C130.1, C132.2, JP33.2, R130.1, U65.2, U65.3, U65.4, U66.2
GND33: C134.1, C136.2, JP34.2, R134.1, U67.2, U67.3, U67.4, U68.2
GND34: C138.1, C140.2, JP35.2, R138.1, U69.2, U69.3, U69.4, U70.2
GND35: C142.1, C144.2, JP36.2, R142.1, U71.2, U71.3, U71.4, U72.2
GND36: C146.1, C148.2, JP37.2, R146.1, U73.2, U73.3, U73.4, U74.2
GND37: C150.1, C152.2, JP38.2, R150.1, U75.2, U75.3, U75.4, U76.2
GND38: C154.1, C156.2, JP39.2, R154.1, U77.2, U77.3, U77.4, U78.2
GND39: C158.1, C160.2, JP40.2, R158.1, U79.2, U79.3, U79.4, U80.2
GND40: C162.1, C164.2, JP41.2, R162.1, U81.2, U81.3, U81.4, U82.2
GND41: C166.1, C168.2, JP42.2, R166.1, U83.2, U83.3, U83.4, U84.2
GND42: C170.1, C172.2, JP43.2, R170.1, U85.2, U85.3, U85.4, U86.2
GND43: C174.1, C176.2, JP44.2, R174.1, U87.2, U87.3, U87.4, U88.2
GND44: C178.1, C180.2, JP45.2, R178.1, U89.2, U89.3, U89.4, U90.2
GND45: C182.1, C184.2, JP46.2, R182.1, U91.2, U91.3, U91.4, U92.2
GND46: C186.1, C188.2, JP47.2, R186.1, U93.2, U93.3, U93.4, U94.2
GND47: C190.1, C192.2, JP48.2, R190.1, U95.2, U95.3, U95.4, U96.2
GND48: C194.1, C196.2, JP49.2, R194.1, U97.2, U97.3, U97.4, U98.2
GND49: C198.1, C200.2, JP50.2, R198.1, U99.2, U99.3, U99.4, U100.2
GND50: C202.1, C204.2, JP51.2, R202.1, U101.2, U101.3, U101.4, U102.2
GND51: C206.1, C208.2, JP52.2, R206.1, U103.2, U103.3, U103.4, U104.2
GND52: C210.1, C212.2, JP53.2, R210.1, U105.2, U105.3, U105.4, U106.2
GND53: C214.1, C216.2, JP54.2, R214.1, U107.2, U107.3, U107.4, U108.2
GND54: C218.1, C220.2, JP55.2, R218.1, U109.2, U109.3, U109.4, U110.2
GND55: C222.1, C224.2, JP56.2, R222.1, U111.2, U111.3, U111.4, U112.2
GND56: C226.1, C228.2, JP57.2, R226.1, U113.2, U113.3, U113.4, U114.2
GND57: C230.1, C232.2, JP58.2, R230.1, U115.2, U115.3, U115.4, U116.2
GND58: C234.1, C236.2, JP59.2, R234.1, U117.2, U117.3, U117.4, U118.2
GND59: C238.1, C240.2, JP60.2, R238.1, U119.2, U119.3, U119.4, U120.2
GND60: C242.1, C244.2, JP61.2, R242.1, U121.2, U121.3, U121.4, U122.2
GND61: C246.1, C248.2, JP62.2, R246.1, U123.2, U123.3, U123.4, U124.2
GND62: C250.1, C252.2, JP63.2, R250.1, U125.2, U125.3, U125.4, U126.2
GND63: C254.1, C256.2, JP64.2, R254.1, U127.2, U127.3, U127.4, U128.2
GND64: C258.1, C260.2, JP65.2, R258.1, U129.2, U129.3, U129.4, U130.2
GND65: C262.1, C264.2, JP66.2, R262.1, U131.2, U131.3, U131.4, U132.2
GND66: C266.1, C268.2, JP67.2, R266.1, U133.2, U133.3, U133.4, U134.2
GND67: C270.1, C272.2, JP68.2, R270.1, U135.2, U135.3, U135.4, U136.2
GND68: C274.1, C276.2, JP69.2, R274.1, U137.2, U137.3, U137.4, U138.2
GND69: C278.1, C280.2, JP70.2, R278.1, U139.2, U139.3, U139.4, U140.2
GND70: C282.1, C284.2, JP71.2, R282.1, U141.2, U141.3, U141.4, U142.2
GND71: C286.1, C288.2, JP72.2, R286.1, U143.2, U143.3, U143.4, U144.2
GND72: C290.1, C292.2, JP73.2, R290.1, U145.2, U145.3, U145.4, U146.2
GND73: C294.1, C296.2, JP74.2, R294.1, U147.2, U147.3, U147.4, U148.2
GND74: C298.1, C300.2, JP75.2, R298.1, U149.2, U149.3, U149.4, U150.2
GND75: C302.1, C304.2, JP76.2, R302.1, U151.2, U151.3, U151.4, U152.2
GND76: C306.1, C308.2, JP77.2, R306.1, U153.2, U153.3, U153.4, U154.2
GND77: C310.1, C312.2, JP78.2, R310.1, U155.2, U155.3, U155.4, U156.2
GND78: C314.1, C316.2, JP79.2, R314.1, U157.2, U157.3, U157.4, U158.2
GND79: C318.1, C320.2, JP80.2, R318.1, U159.2, U159.3, U159.4, U160.2
GND80: C322.1, C324.2, JP81.2, R322.1, U161.2, U161.3, U161.4, U162.2
GND81: C326.1, C328.2, JP82.2, R326.1, U163.2, U163.3, U163.4, U164.2
GND82: C330.1, C332.2, JP83.2, R330.1, U165.2, U165.3, U165.4, U166.2
GND83: C334.1, C336.2, JP84.2, R334.1, U167.2, U167.3, U167.4, U168.2
GND84: C338.1, C340.2, JP85.2, R338.1, U169.2, U169.3, U169.4, U170.2
GND85: C342.1, C344.2, JP86.2, R342.1, U171.2, U171.3, U171.4, U172.2
GND86: C346.1, C348.2, JP87.2, R346.1, U173.2, U173.3, U173.4, U174.2
GND87: C350.1, C352.2, JP88.2, R350.1, U175.2, U175.3, U175.4, U176.2
GND88: C354.1, C356.2, JP89.2, R354.1, U177.2, U177.3, U177.4, U178.2
GND89: C358.1, C360.2, JP90.2, R358.1, U179.2, U179.3, U179.4, U180.2
GND90: C362.1, C364.2, JP91.2, R362.1, U181.2, U181.3, U181.4, U182.2
GND91: C366.1, C368.2, JP92.2, R366.1, U183.2, U183.3, U183.4, U184.2
GND92: C370.1, C372.2, JP93.2, R370.1, U185.2, U185.3, U185.4, U186.2
GND93: C374.1, C376.2, JP94.2, R374.1, U187.2, U187.3, U187.4, U188.2
GND94: C378.1, C380.2, JP95.2, R378.1, U189.2, U189.3, U189.4, U190.2
GND95: C382.1, C384.2, JP96.2, R382.1, U191.2, U191.3, U191.4, U192.2
GND96: C386.1, C388.2, JP97.2, R386.1, U193.2, U193.3, U193.4, U194.2
GND97: C390.1, C392.2, JP98.2, R390.1, U195.2, U195.3, U195.4, U196.2
GND98: C394.1, C396.2, JP99.2, R394.1, U197.2, U197.3, U197.4, U198.2
GND99: C398.1, C400.2, JP100.2, R398.1, U199.2, U199.3, U199.4, U200.2
GND100: C402.1, C404.2, JP101.2, R402.1, U201.2, U201.3, U201.4, U202.2
GND101: C406.1, C408.2, JP102.2, R406.1, U203.2, U203.3, U203.4, U204.2
GND102: C410.1, C412.2, JP103.2, R410.1, U205.2, U205.3, U205.4, U206.2
GND103: C414.1, C416.2, JP104.2, R414.1, U207.2, U207.3, U207.4, U208.2
GND104: C418.1, C420.2, JP105.2, R418.1, U209.2, U209.3, U209.4, U210.2
GND105: C422.1, C424.2, JP106.2, R422.1, U211.2, U211.3, U211.4, U212.2
GND106: C426.1, C428.2, JP107.2, R426.1, U213.2, U213.3, U213.4, U214.2
GND107: C430.1, C432.2, JP108.2, R430.1, U215.2, U215.3, U215.4, U216.2
GND108: C434.1, C436.2, JP109.2, R434.1, U217.2, U217.3, U217.4, U218.2
GND109: C438.1, C440.2, JP110.2, R438.1, U219.2, U219.3, U219.4, U220.2
GND110: C442.1, C444.2, JP111.2, R442.1, U221.2, U221.3, U221.4, U222.2
GND111: C446.1, C448.2, JP112.2, R446.1, U223.2, U223.3, U223.4, U224.2
GND112: C450.1, C452.2, JP113.2, R450.1, U225.2, U225.3, U225.4, U226.2
GND113: C454.1, C456.2, JP114.2, R454.1, U227.2, U227.3, U227.4, U228.2
GND114: C458.1, C460.2, JP115.2, R458.1, U229.2, U229.3, U229.4, U230.2
GND115: C462.1, C464.2, JP116.2, R462.1, U231.2, U231.3, U231.4, U232.2
GND116: C466.1, C468.2, JP117.2, R466.1, U233.2, U233.3, U233.4, U234.2
GND117: C470.1, C472.2, JP118.2, R470.1, U235.2, U235.3, U235.4, U236.2
GND118: C474.1, C476.2, JP119.2, R474.1, U237.2, U237.3, U237.4, U238.2
GND119: C478.1, C480.2, JP120.2, R478.1, U239.2, U239.3, U239.4, U240.2
unnamed: C1.1, U2.1
unnamed: C3.1, R3.1, R4.2, U1.4
unnamed: C7.1, U3.1
unnamed: C5.1, R7.1, R8.2, U4.4
unnamed: C7.2, R7.2
unnamed: C1.2, R3.2
unnamed: C2.1, R1.1, R2.2, U1.3
unnamed: C8.1, R5.1, R6.2, U4.3
unnamed: C11.1, U5.1
unnamed: C9.1, R11.1, R12.2, U6.4
unnamed: C11.2, R11.2
unnamed: C12.1, R9.1, R10.2, U6.3
unnamed: C15.1, U7.1
unnamed: C13.1, R15.1, R16.2, U8.4
unnamed: C15.2, R15.2
unnamed: C16.1, R13.1, R14.2, U8.3
unnamed: C19.1, U9.1
unnamed: C17.1, R19.1, R20.2, U10.4
unnamed: C19.2, R19.2
unnamed: C20.1, R17.1, R18.2, U10.3
unnamed: C23.1, U11.1
unnamed: C21.1, R23.1, R24.2, U12.4
unnamed: C23.2, R23.2
unnamed: C24.1, R21.1, R22.2, U12.3
unnamed: C27.1, U13.1
unnamed: C25.1, R27.1, R28.2, U14.4
unnamed: C27.2, R27.2
unnamed: C28.1, R25.1, R26.2, U14.3
unnamed: C31.1, U15.1
unnamed: C29.1, R31.1, R32.2, U16.4
unnamed: C31.2, R31.2
unnamed: C32.1, R29.1, R30.2, U16.3
unnamed: C35.1, U17.1
unnamed: C33.1, R35.1, R36.2, U18.4
unnamed: C35.2, R35.2
unnamed: C36.1, R33.1, R34.2, U18.3
unnamed: C39.1, U19.1
unnamed: C37.1, R39.1, R40.2, U20.4
unnamed: C39.2, R39.2
unnamed: C40.1, R37.1, R38.2, U20.3
unnamed: C43.1, U21.1
unnamed: C41.1, R43.1, R44.2, U22.4
unnamed: C43.2, R43.2
unnamed: C44.1, R41.1, R42.2, U22.3
unnamed: C47.1, U23.1
unnamed: C45.1, R47.1, R48.2, U24.4
unnamed: C47.2, R47.2
unnamed: C48.1, R45.1, R46.2, U24.3
unnamed: C51.1, U25.1
unnamed: C49.1, R51.1, R52.2, U26.4
unnamed: C51.2, R51.2
unnamed: C52.1, R49.1, R50.2, U26.3
unnamed: C55.1, U27.1
unnamed: C53.1, R55.1, R56.2, U28.4
unnamed: C55.2, R55.2
unnamed: C56.1, R53.1, R54.2, U28.3
unnamed: C59.1, U29.1
unnamed: C57.1, R59.1, R60.2, U30.4
unnamed: C59.2, R59.2
unnamed: C60.1, R57.1, R58.2, U30.3
unnamed: C63.1, U31.1
unnamed: C61.1, R63.1, R64.2, U32.4
unnamed: C63.2, R63.2
unnamed: C64.1, R61.1, R62.2, U32.3
unnamed: C67.1, U33.1
unnamed: C65.1, R67.1, R68.2, U34.4
unnamed: C67.2, R67.2
unnamed: C68.1, R65.1, R66.2, U34.3
unnamed: C71.1, U35.1
unnamed: C69.1, R71.1, R72.2, U36.4
unnamed: C71.2, R71.2
unnamed: C72.1, R69.1, R70.2, U36.3
unnamed: C75.1, U37.1
unnamed: C73.1, R75.1, R76.2, U38.4
unnamed: C75.2, R75.2
unnamed: C76.1, R73.1, R74.2, U38.3
unnamed: C79.1, U39.1
unnamed: C77.1, R79.1, R80.2, U40.4
unnamed: C79.2, R79.2
unnamed: C80.1, R77.1, R78.2, U40.3
unnamed: C83.1, U41.1
unnamed: C81.1, R83.1, R84.2, U42.4
unnamed: C83.2, R83.2
unnamed: C84.1, R81.1, R82.2, U42.3
unnamed: C87.1, U43.1
unnamed: C85.1, R87.1, R88.2, U44.4
unnamed: C87.2, R87.2
unnamed: C88.1, R85.1, R86.2, U44.3
unnamed: C91.1, U45.1
unnamed: C89.1, R91.1, R92.2, U46.4
unnamed: C91.2, R91.2
unnamed: C92.1, R89.1, R90.2, U46.3
unnamed: C95.1, U47.1
unnamed: C93.1, R95.1, R96.2, U48.4
unnamed: C95.2, R95.2
unnamed: C96.1, R93.1, R94.2, U48.3
unnamed: C99.1, U49.1
unnamed: C97.1, R99.1, R100.2, U50.4
unnamed: C99.2, R99.2
unnamed: C100.1, R97.1, R98.2, U50.3
unnamed: C103.1, U51.1
unnamed: C101.1, R103.1, R104.2, U52.4
unnamed: C103.2, R103.2
unnamed: C104.1, R101.1, R102.2, U52.3
unnamed: C107.1, U53.1
unnamed: C105.1, R107.1, R108.2, U54.4
unnamed: C107.2, R107.2
unnamed: C108.1, R105.1, R106.2, U54.3
unnamed: C111.1, U55.1
unnamed: C109.1, R111.1, R112.2, U56.4
unnamed: C111.2, R111.2
unnamed: C112.1, R109.1, R110.2, U56.3
unnamed: C115.1, U57.1
unnamed: C113.1, R115.1, R116.2, U58.4
unnamed: C115.2, R115.2
unnamed: C116.1, R113.1, R114.2, U58.3
unnamed: C119.1, U59.1
unnamed: C117.1, R119.1, R120.2, U60.4
unnamed: C119.2, R119.2
unnamed: C120.1, R117.1, R118.2, U60.3
unnamed: C123.1, U61.1
unnamed: C121.1, R123.1, R124.2, U62.4
unnamed: C123.2, R123.2
unnamed: C124.1, R121.1, R122.2, U62.3
unnamed: C127.1, U63.1
unnamed: C125.1, R127.1, R128.2, U64.4
unnamed: C127.2, R127.2
unnamed: C128.1, R125.1, R126.2, U64.3
unnamed: C131.1, U65.1
unnamed: C129.1, R131.1, R132.2, U66.4
unnamed: C131.2, R131.2
unnamed: C132.1, R129.1, R130.2, U66.3
unnamed: C135.1, U67.1
unnamed: C133.1, R135.1, R136.2, U68.4
unnamed: C135.2, R135.2
unnamed: C136.1, R133.1, R134.2, U68.3
unnamed: C139.1, U69.1
unnamed: C137.1, R139.1, R140.2, U70.4
unnamed: C139.2, R139.2
unnamed: C140.1, R137.1, R138.2, U70.3
unnamed: C143.1, U71.1
unnamed: C141.1, R143.1, R144.2, U72.4
unnamed: C143.2, R143.2
unnamed: C144.1, R141.1, R142.2, U72.3
unnamed: C147.1, U73.1
unnamed: C145.1, R147.1, R148.2, U74.4
unnamed: C147.2, R147.2
unnamed: C148.1, R145.1, R146.2, U74.3
unnamed: C151.1, U75.1
unnamed: C149.1, R151.1, R152.2, U76.4
unnamed: C151.2, R151.2
unnamed: C152.1, R149.1, R150.2, U76.3
unnamed: C155.1, U77.1
unnamed: C153.1, R155.1, R156.2, U78.4
unnamed: C155.2, R155.2
unnamed: C156.1, R153.1, R154.2, U78.3
unnamed: C159.1, U79.1
unnamed: C157.1, R159.1, R160.2, U80.4
unnamed: C159.2, R159.2
unnamed: C160.1, R157.1, R158.2, U80.3
unnamed: C163.1, U81.1
unnamed: C161.1, R163.1, R164.2, U82.4
unnamed: C163.2, R163.2
unnamed: C164.1, R161.1, R162.2, U82.3
unnamed: C167.1, U83.1
unnamed: C165.1, R167.1, R168.2, U84.4
unnamed: C167.2, R167.2
unnamed: C168.1, R165.1, R166.2, U84.3
unnamed: C171.1, U85.1
unnamed: C169.1, R171.1, R172.2, U86.4
unnamed: C171.2, R171.2
unnamed: C172.1, R169.1, R170.2, U86.3
unnamed: C175.1, U87.1
unnamed: C173.1, R175.1, R176.2, U88.4
unnamed: C175.2, R175.2
unnamed: C176.1, R173.1, R174.2, U88.3
unnamed: C179.1, U89.1
unnamed: C177.1, R179.1, R180.2, U90.4
unnamed: C179.2, R179.2
unnamed: C180.1, R177.1, R178.2, U90.3
unnamed: C183.1, U91.1
unnamed: C181.1, R183.1, R184.2, U92.4
unnamed: C183.2, R183.2
unnamed: C184.1, R181.1, R182.2, U92.3
unnamed: C187.1, U93.1
unnamed: C185.1, R187.1, R188.2, U94.4
unnamed: C187.2, R187.2
unnamed: C188.1, R185.1, R186.2, U94.3
unnamed: C191.1, U95.1
unnamed: C189.1, R191.1, R192.2, U96.4
unnamed: C191.2, R191.2
unnamed: C192.1, R189.1, R190.2, U96.3
unnamed: C195.1, U97.1
unnamed: C193.1, R195.1, R196.2, U98.4
unnamed: C195.2, R195.2
unnamed: C196.1, R193.1, R194.2, U98.3
unnamed: C199.1, U99.1
unnamed: C197.1, R199.1, R200.2, U100.4
unnamed: C199.2, R199.2
unnamed: C200.1, R197.1, R198.2, U100.3
unnamed: C203.1, U101.1
unnamed: C201.1, R203.1, R204.2, U102.4
unnamed: C203.2, R203.2
unnamed: C204.1, R201.1, R202.2, U102.3
unnamed: C207.1, U103.1
unnamed: C205.1, R207.1, R208.2, U104.4
unnamed: C207.2, R207.2
unnamed: C208.1, R205.1, R206.2, U104.3
unnamed: C211.1, U105.1
unnamed: C209.1, R211.1, R212.2, U106.4
unnamed: C211.2, R211.2
unnamed: C212.1, R209.1, R210.2, U106.3
unnamed: C215.1, U107.1
unnamed: C213.1, R215.1, R216.2, U108.4
unnamed: C215.2, R215.2
unnamed: C216.1, R213.1, R214.2, U108.3
unnamed: C219.1, U109.1
unnamed: C217.1, R219.1, R220.2, U110.4
unnamed: C219.2, R219.2
unnamed: C220.1, R217.1, R218.2, U110.3
unnamed: C223.1, U111.1
unnamed: C221.1, R223.1, R224.2, U112.4
unnamed: C223.2, R223.2
unnamed: C224.1, R221.1, R222.2, U112.3
unnamed: C227.1, U113.1
unnamed: C225.1, R227.1, R228.2, U114.4
unnamed: C227.2, R227.2
unnamed: C228.1, R225.1, R226.2, U114.3
unnamed: C231.1, U115.1
unnamed: C229.1, R231.1, R232.2, U116.4
unnamed: C231.2, R231.2
unnamed: C232.1, R229.1, R230.2, U116.3
unnamed: C235.1, U117.1
unnamed: C233.1, R235.1, R236.2, U118.4
unnamed: C235.2, R235.2
unnamed: C236.1, R233.1, R234.2, U118.3
unnamed: C239.1, U119.1
unnamed: C237.1, R239.1, R240.2, U120.4
unnamed: C239.2, R239.2
unnamed: C240.1, R237.1, R238.2, U120.3
unnamed: C243.1, U121.1
unnamed: C241.1, R243.1, R244.2, U122.4
unnamed: C243.2, R243.2
unnamed: C244.1, R241.1, R242.2, U122.3
unnamed: C247.1, U123.1
unnamed: C245.1, R247.1, R248.2, U124.4
unnamed: C247.2, R247.2
unnamed: C248.1, R245.1, R246.2, U124.3
unnamed: C251.1, U125.1
unnamed: C249.1, R251.1, R252.2, U126.4
unnamed: C251.2, R251.2
unnamed: C252.1, R249.1, R250.2, U126.3
unnamed: C255.1, U127.1
unnamed: C253.1, R255.1, R256.2, U128.4
unnamed: C255.2, R255.2
unnamed: C256.1, R253.1, R254.2, U128.3
unnamed: C259.1, U129.1
unnamed: C257.1, R259.1, R260.2, U130.4
unnamed: C259.2, R259.2
unnamed: C260.1, R257.1, R258.2, U130.3
unnamed: C263.1, U131.1
unnamed: C261.1, R263.1, R264.2, U132.4
unnamed: C263.2, R263.2
unnamed: C264.1, R261.1, R262.2, U132.3
unnamed: C267.1, U133.1
unnamed: C265.1, R267.1, R268.2, U134.4
unnamed: C267.2, R267.2
unnamed: C268.1, R265.1, R266.2, U134.3
unnamed: C271.1, U135.1
unnamed: C269.1, R271.1, R272.2, U136.4
unnamed: C271.2, R271.2
unnamed: C272.1, R269.1, R270.2, U136.3
unnamed: C275.1, U137.1
unnamed: C273.1, R275.1, R276.2, U138.4
unnamed: C275.2, R275.2
unnamed: C276.1, R273.1, R274.2, U138.3
unnamed: C279.1, U139.1
unnamed: C277.1, R279.1, R280.2, U140.4
unnamed: C279.2, R279.2
unnamed: C280.1, R277.1, R278.2, U140.3
unnamed: C283.1, U141.1
unnamed: C281.1, R283.1, R284.2, U142.4
unnamed: C283.2, R283.2
unnamed: C284.1, R281.1, R282.2, U142.3
unnamed: C287.1, U143.1
unnamed: C285.1, R287.1, R288.2, U144.4
unnamed: C287.2, R287.2
unnamed: C288.1, R285.1, R286.2, U144.3
unnamed: C291.1, U145.1
unnamed: C289.1, R291.1, R292.2, U146.4
unnamed: C291.2, R291.2
unnamed: C292.1, R289.1, R290.2, U146.3
unnamed: C295.1, U147.1
unnamed: C293.1, R295.1, R296.2, U148.4
unnamed: C295.2, R295.2
unnamed: C296.1, R293.1, R294.2, U148.3
unnamed: C299.1, U149.1
unnamed: C297.1, R299.1, R300.2, U150.4
unnamed: C299.2, R299.2
unnamed: C300.1, R297.1, R298.2, U150.3
unnamed: C303.1, U151.1
unnamed: C301.1, R303.1, R304.2, U152.4
unnamed: C303.2, R303.2
unnamed: C304.1, R301.1, R302.2, U152.3
unnamed: C307.1, U153.1
unnamed: C305.1, R307.1, R308.2, U154.4
unnamed: C307.2, R307.2
unnamed: C308.1, R305.1, R306.2, U154.3
unnamed: C311.1, U155.1
unnamed: C309.1, R311.1, R312.2, U156.4
unnamed: C311.2, R311.2
unnamed: C312.1, R309.1, R310.2, U156.3
unnamed: C315.1, U157.1
unnamed: C313.1, R315.1, R316.2, U158.4
unnamed: C315.2, R315.2
unnamed: C316.1, R313.1, R314.2, U158.3
unnamed: C319.1, U159.1
unnamed: C317.1, R319.1, R320.2, U160.4
unnamed: C319.2, R319.2
unnamed: C320.1, R317.1, R318.2, U160.3
unnamed: C323.1, U161.1
unnamed: C321.1, R323.1, R324.2, U162.4
unnamed: C323.2, R323.2
unnamed: C324.1, R321.1, R322.2, U162.3
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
